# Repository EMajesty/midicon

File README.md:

# MIDI Controller — MCU Pinout and Wiring Reference

MCU: Arduino Mega 2560 Pro  
Logic voltage: 5 V

## 1. MCU Pin Assignments

| Arduino Pin | Net | Function |
|---|---|---|
| D3 | E1_PB | Encoder 1 push button |
| D5 | E1_A | Encoder 1 channel A |
| D7 | E1_B | Encoder 1 channel B |
| D9 | E2_PB | Encoder 2 push button |
| D11 | E2_A | Encoder 2 channel A |
| D14 | E2_B | Encoder 2 channel B |
| D15 | E3_PB | Encoder 3 push button |
| D17 | E3_A | Encoder 3 channel A |
| D18 | MIDI_OUT | MIDI output (TX1) |
| D19 | MIDI_IN | MIDI input (RX1) |
| D21 | E3_B | Encoder 3 channel B |
| D23 | E4_PB | Encoder 4 push button |
| D24 | C1 | Matrix column 1 |
| D25 | E4_A | Encoder 4 channel A |
| D26 | C2 | Matrix column 2 |
| D27 | E4_B | Encoder 4 channel B |
| D28 | C3 | Matrix column 3 |
| D30 | C4 | Matrix column 4 |
| D32 | LEDS | WS2812B data |
| D33 | F1 | Function button 1 |
| D35 | F2 | Function button 2 |
| D36 | LCD_RS | LCD register select |
| D37 | F3 | Function button 3 |
| D38 | LCD_E | LCD enable |
| D39 | F4 | Function button 4 |
| D40 | LCD_DB4 | LCD data bit 4 |
| D41 | R1 | Matrix row 1 |
| D42 | LCD_DB5 | LCD data bit 5 |
| D43 | R2 | Matrix row 2 |
| D44 | LCD_DB6 | LCD data bit 6 |
| D45 | R3 | Matrix row 3 |
| D46 | LCD_DB7 | LCD data bit 7 |
| D47 | R4 | Matrix row 4 |
| A0 | ADC_F1 | Fader 1 |
| A2 | ADC_F2 | Fader 2 |
| A4 | ADC_F3 | Fader 3 |
| A6 | ADC_F4 | Fader 4 |
| A8 | ADC_J1X | Joystick 1 X |
| A10 | ADC_J1Y | Joystick 1 Y |
| A12 | ADC_J2X | Joystick 2 X |
| A14 | ADC_J2Y | Joystick 2 Y |

D0/D1 are reserved for USB serial debugging.

## 2. Rotary Encoders

Four rotary encoders with integrated push buttons.

| Contact | Connection |
|---|---|
| A | E*_A MCU input |
| B | E*_B MCU input |
| Common | GND |
| Push button terminal 1 | E*_PB MCU input |
| Push button terminal 2 | GND |

- All 12 inputs use `INPUT_PULLUP`.
- Rotary contacts pull their respective inputs LOW when closed.
- Push buttons are active LOW.
- Quadrature decoding and debouncing are handled in firmware.

## 3. Function Buttons

Four independent momentary buttons.

| Contact | Connection |
|---|---|
| Terminal 1 | F1–F4 MCU input |
| Terminal 2 | GND |

- Configure as `INPUT_PULLUP`.
- Pressed = LOW.

## 4. Button Matrix

4×4 matrix with one diode per button.

| Row | C1 (D24) | C2 (D26) | C3 (D28) | C4 (D30) |
|---|---|---|---|---|
| R1 (D41) | SW1 | SW2 | SW3 | SW4 |
| R2 (D43) | SW5 | SW6 | SW7 | SW8 |
| R3 (D45) | SW9 | SW10 | SW11 | SW12 |
| R4 (D47) | SW13 | SW14 | SW15 | SW16 |

### Wiring

Each button is wired:

`Column → Switch → Diode anode → Diode cathode → Row`

- Diode cathode (striped end) faces the row.
- One diode per switch prevents ghosting.
- Columns are configured as `INPUT_PULLUP`.
- Scan by driving one row LOW at a time.
- Inactive rows are high-impedance (`INPUT`).
- A pressed button on the active row reads LOW at its column.

## 5. Analog Controls

Four stereo faders (one track used per fader) and two dual-axis joysticks.

| Control | ADC Pin |
|---|---|
| Fader 1 | A0 |
| Fader 2 | A2 |
| Fader 3 | A4 |
| Fader 4 | A6 |
| Joystick 1 X | A8 |
| Joystick 1 Y | A10 |
| Joystick 2 X | A12 |
| Joystick 2 Y | A14 |

### Wiring

Each potentiometer:

| Terminal | Connection |
|---|---|
| End 1 | +5 V |
| Wiper | ADC input |
| End 3 | GND |

- ADC range: 0–1023.
- Reversing the outer terminals reverses the control direction.
- Unused tracks of stereo faders are left unconnected.
- Joystick axes each use one potentiometer.

## 6. WS2812B LEDs

Four addressable RGB LEDs connected in series.

| Signal | Connection |
|---|---|
| First LED DIN | D32 (LEDS) |
| Each LED DOUT | Next LED DIN |
| All VDD | +5 V |
| All VSS | GND |
| Final LED DOUT | Unconnected |

All LEDs are controlled through one MCU pin.

## 7. LCD

20×2 character LCD, 4-bit parallel interface.

Module markings: Winstar WDH0048-TMI-ET#00 / Forewin 2002AE-1.

The following assumes a standard HD44780-compatible 16-pin interface.

| LCD Pin | Signal | Connection |
|---|---|---|
| 1 | VSS | GND |
| 2 | VDD | +5 V |
| 3 | VO | Contrast potentiometer wiper |
| 4 | RS | D36 |
| 5 | R/W | GND |
| 6 | E | D38 |
| 7–10 | DB0–DB3 | Unconnected |
| 11 | DB4 | D40 |
| 12 | DB5 | D42 |
| 13 | DB6 | D44 |
| 14 | DB7 | D46 |
| 15 | LED+ | +5 V (verify current limiting) |
| 16 | LED− | GND |

### Contrast potentiometer (RV9)

| Terminal | Connection |
|---|---|
| End 1 | +5 V |
| Wiper | LCD VO |
| End 3 | GND |

Firmware initialization:

`LiquidCrystal lcd(36, 38, 40, 42, 44, 46);`

## 8. MIDI Input

5-pin DIN MIDI input using a 6N137 optocoupler.

## 9. MIDI Output

5-pin DIN MIDI output driven by hardware UART1.

Firmware:

`Serial1.begin(31250);`

## 10. Power Supply

9 V DC input regulated to 5 V using an L7805.

| Component | Connection |
|---|---|
| Barrel jack positive | +9 V |
| Barrel jack negative | GND |
| L7805 IN | +9 V |
| L7805 GND | GND |
| L7805 OUT | +5 V |
| C2 | Input decoupling |
| C1 | Output decoupling |

The +5 V rail supplies the MCU, controls, LCD, MIDI circuitry and LEDs.

## Firmware and configurator

The v1 firmware is a standalone, four-page configurable MIDI controller. Build it with `pio run -d firmware`; see [firmware/README.md](firmware/README.md) for operation, EEPROM layout, MIDI conventions, and the USB protocol.

The native Python configurator provides JSON validation/import/export, device upload/download, explicit EEPROM save/reload, and a PySide6 GUI:

```sh
python -m pip install -r requirements.txt
python -m configurator validate config/default.json
python -m configurator gui
```

See [configurator/README.md](configurator/README.md) for all commands and [docs/hardware-test-checklist.md](docs/hardware-test-checklist.md) for physical verification.

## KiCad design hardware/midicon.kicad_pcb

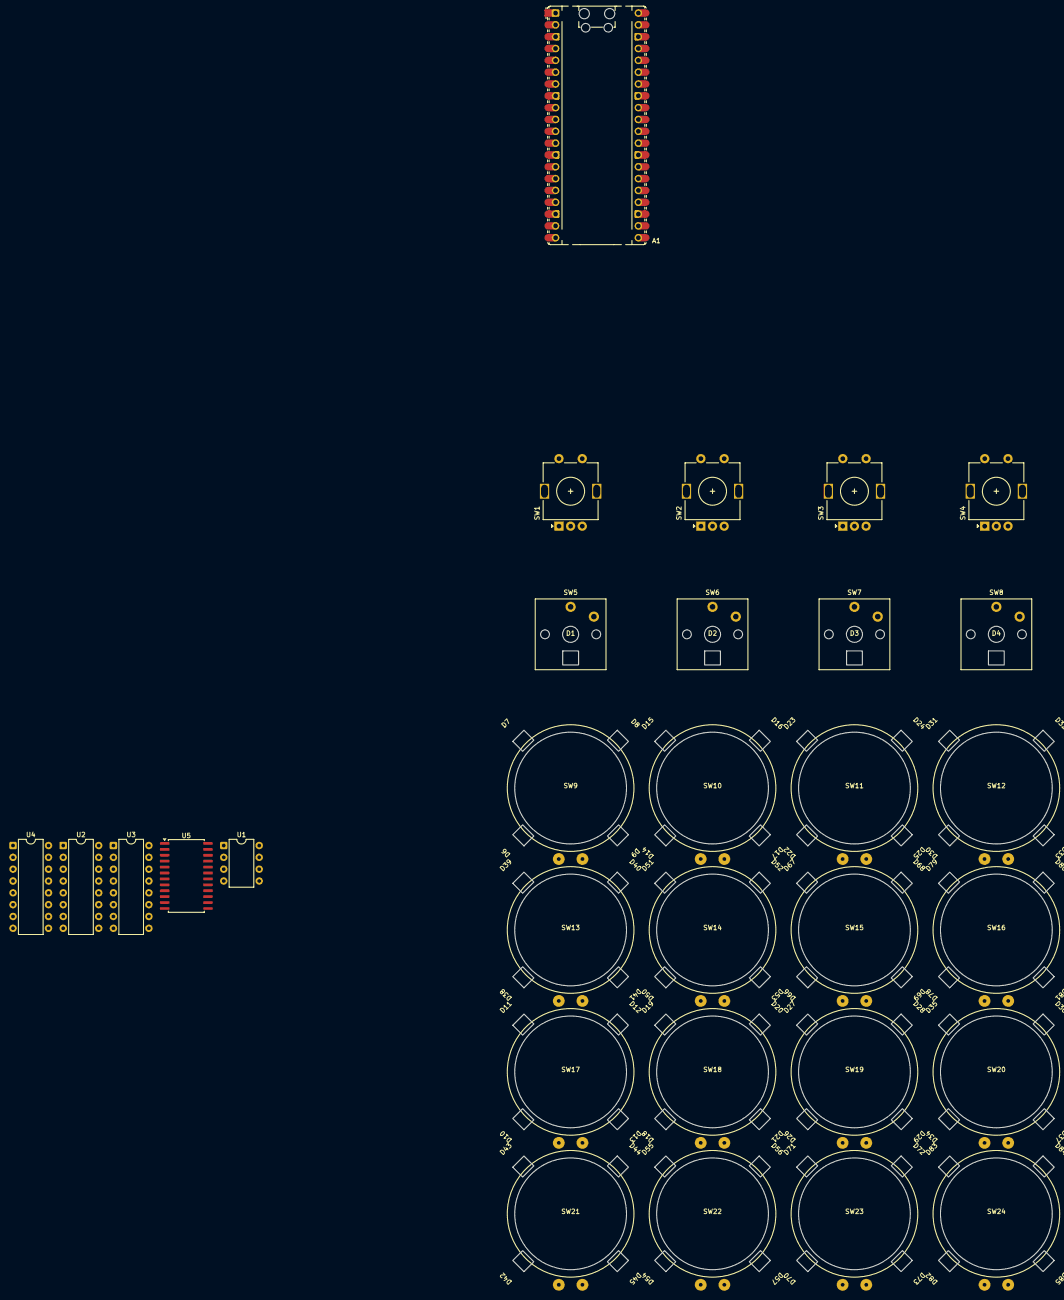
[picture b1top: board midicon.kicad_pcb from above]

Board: 2 copper layers, 98 parts (0 on the bottom side), 103 nets, no tracks yet.

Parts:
A1: RaspberryPi_Pico; RaspberryPi_Pico_Common_Unspecified
D1, D2, D3, D4, D6, D7, D8, D9, D10, D11, D12, D13, D14, D15, D16, D17, D18, D19, D20, D21, D22, D23, D24, D25, D26, D27, D28, D29, D30, D31, D32, D33, D34, D35, D36, D37, D38, D39, D40, D41, D42, D43, D44, D45, D50, D51, D52, D53, D54, D55, D56, D57, D66, D67, D68, D69, D70, D71, D72, D73, D78, D79, D80, D81, D82, D83, D84, D85: WS2812B; SK6812MINIE
SW1, SW2, SW3, SW4: RotaryEncoder_Switch; RotaryEncoder_Alps_EC11E-Switch_Vertical_H20mm
SW5, SW6, SW7, SW8: SW_Push; SW_Kailh_Choc_V1
SW9, SW10, SW11, SW12, SW13, SW14, SW15, SW16, SW17, SW18, SW19, SW20, SW21, SW22, SW23, SW24: SW_Push; Arcade Button
U1: 6N138; DIP-8_W7.62mm
U2, U3: 74HC165; DIP-16_W7.62mm
U4: 74HC595; DIP-16_W7.62mm
U5: HEF4067BT; SOIC-24W_7.5x15.4mm_P1.27mm

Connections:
165_CLK: A1.4 (GPIO2), U2.2 (CP), U3.2 (CP)
165_DATA: A1.6 (GPIO4), U3.9 (Q7)
165_LOAD: A1.5 (GPIO3), U2.1 (~PL), U3.1 (~PL)
595_CLK: A1.9 (GPIO6), U4.11 (SRCLK)
595_DATA: A1.7 (GPIO5), U4.14 (SER)
595_LATCH: A1.10 (GPIO7), U4.12 (RCLK)
4067_S0: A1.11 (GPIO8), U5.10 (A0)
4067_S1: A1.12 (GPIO9), U5.11 (A1)
4067_S2: A1.14 (GPIO10), U5.14 (A2)
4067_S3: A1.15 (GPIO11), U5.13 (A3)
4067_SIG: A1.31 (GPIO26_ADC0), U5.1 (Z)
+3.3V: A1.36 (3V3), U2.16 (VCC), U3.16 (VCC), U4.10 (~SRCLR), U4.16 (VCC), U5.24 (VDD)
+5V: A1.40 (VBUS), D1.1 (VDD), D2.1 (VDD), D3.1 (VDD), D4.1 (VDD), D6.1 (VDD), D7.1 (VDD), D8.1 (VDD), D9.1 (VDD), D10.1 (VDD), D11.1 (VDD), D12.1 (VDD), D13.1 (VDD), D14.1 (VDD), D15.1 (VDD), D16.1 (VDD), D17.1 (VDD), D18.1 (VDD), D19.1 (VDD), D20.1 (VDD), D21.1 (VDD), D22.1 (VDD), D23.1 (VDD), D24.1 (VDD), D25.1 (VDD), D26.1 (VDD), D27.1 (VDD), D28.1 (VDD), D29.1 (VDD), D30.1 (VDD), D31.1 (VDD), D32.1 (VDD), D33.1 (VDD), D34.1 (VDD), D35.1 (VDD), D36.1 (VDD), D37.1 (VDD), D38.1 (VDD), D39.1 (VDD), D40.1 (VDD), D41.1 (VDD), D42.1 (VDD), D43.1 (VDD), D44.1 (VDD), D45.1 (VDD), D50.1 (VDD), D51.1 (VDD), D52.1 (VDD), D53.1 (VDD), D54.1 (VDD), D55.1 (VDD), D56.1 (VDD), D57.1 (VDD), D66.1 (VDD), D67.1 (VDD), D68.1 (VDD), D69.1 (VDD), D70.1 (VDD), D71.1 (VDD), D72.1 (VDD), D73.1 (VDD), D78.1 (VDD), D79.1 (VDD), D80.1 (VDD), D81.1 (VDD), D82.1 (VDD), D83.1 (VDD), D84.1 (VDD), D85.1 (VDD), U1.8 (VCC)
C1: A1.21 (GPIO16), SW9.1, SW13.1, SW17.1, SW21.1
C2: A1.22 (GPIO17), SW10.1, SW14.1, SW18.1, SW22.1
C3: A1.24 (GPIO18), SW11.1, SW15.1, SW19.1, SW23.1
C4: A1.25 (GPIO19), SW12.1, SW16.1, SW20.1, SW24.1
E1_A: SW1.A, U2.12 (D1)
E1_B: SW1.B, U2.13 (D2)
E1_PB: SW1.S1, U2.11 (D0)
E2_A: SW2.A, U2.3 (D4)
E2_B: SW2.B, U2.4 (D5)
E2_PB: SW2.S1, U2.14 (D3)
E3_A: SW3.A, U2.6 (D7)
E3_B: SW3.B, U3.11 (D0)
E3_PB: SW3.S1, U2.5 (D6)
E4_A: SW4.A, U3.13 (D2)
E4_B: SW4.B, U3.14 (D3)
E4_PB: SW4.S1, U3.12 (D1)
F1: SW5.1, U3.3 (D4)
F2: SW6.1, U3.4 (D5)
F3: SW7.1, U3.5 (D6)
F4: SW8.1, U3.6 (D7)
GND: A1.3 (GND), A1.8 (GND), A1.13 (GND), A1.18 (GND), A1.23 (GND), A1.28 (GND), A1.38 (GND), D1.3 (VSS), D2.3 (VSS), D3.3 (VSS), D4.3 (VSS), D6.3 (VSS), D7.3 (VSS), D8.3 (VSS), D9.3 (VSS), D10.3 (VSS), D11.3 (VSS), D12.3 (VSS), D13.3 (VSS), D14.3 (VSS), D15.3 (VSS), D16.3 (VSS), D17.3 (VSS), D18.3 (VSS), D19.3 (VSS), D20.3 (VSS), D21.3 (VSS), D22.3 (VSS), D23.3 (VSS), D24.3 (VSS), D25.3 (VSS), D26.3 (VSS), D27.3 (VSS), D28.3 (VSS), D29.3 (VSS), D30.3 (VSS), D31.3 (VSS), D32.3 (VSS), D33.3 (VSS), D34.3 (VSS), D35.3 (VSS), D36.3 (VSS), D37.3 (VSS), D38.3 (VSS), D39.3 (VSS), D40.3 (VSS), D41.3 (VSS), D42.3 (VSS), D43.3 (VSS), D44.3 (VSS), D45.3 (VSS), D50.3 (VSS), D51.3 (VSS), D52.3 (VSS), D53.3 (VSS), D54.3 (VSS), D55.3 (VSS), D56.3 (VSS), D57.3 (VSS), D66.3 (VSS), D67.3 (VSS), D68.3 (VSS), D69.3 (VSS), D70.3 (VSS), D71.3 (VSS), D72.3 (VSS), D73.3 (VSS), D78.3 (VSS), D79.3 (VSS), D80.3 (VSS), D81.3 (VSS), D82.3 (VSS), D83.3 (VSS), D84.3 (VSS), D85.3 (VSS), SW1.C, SW1.S2, SW2.C, SW2.S2, SW3.C, SW3.S2, SW4.C, SW4.S2, SW5.2, SW6.2, SW7.2, SW8.2, U1.5 (GND), U2.8 (GND), U2.10 (DS), U2.15 (~CE), U3.8 (GND), U3.15 (~CE), U4.8 (GND), U4.13 (~OE), U5.12 (VSS), U5.15 (~E)
MCU_LEDS: A1.26 (GPIO20), D1.4 (DIN)
MIDI_IN: A1.2 (GPIO1), U1.6 (VO2)
unnamed: D1.2 (DOUT), D2.4 (DIN)
unnamed: D2.2 (DOUT), D3.4 (DIN)
unnamed: D3.2 (DOUT), D4.4 (DIN)
unnamed: D6.2 (DOUT), D7.4 (DIN)
unnamed: D7.2 (DOUT), D8.4 (DIN)
unnamed: D8.2 (DOUT), D9.4 (DIN)
unnamed: D10.4 (DIN), D81.2 (DOUT)
unnamed: D10.2 (DOUT), D11.4 (DIN)
unnamed: D11.2 (DOUT), D12.4 (DIN)
unnamed: D12.2 (DOUT), D13.4 (DIN)
unnamed: D13.2 (DOUT), D18.4 (DIN)
unnamed: D9.2 (DOUT), D14.4 (DIN)
unnamed: D14.2 (DOUT), D15.4 (DIN)
unnamed: D15.2 (DOUT), D16.4 (DIN)
unnamed: D16.2 (DOUT), D17.4 (DIN)
unnamed: D17.2 (DOUT), D22.4 (DIN)
unnamed: D18.2 (DOUT), D19.4 (DIN)
unnamed: D19.2 (DOUT), D20.4 (DIN)
unnamed: D20.2 (DOUT), D21.4 (DIN)
unnamed: D21.2 (DOUT), D26.4 (DIN)
unnamed: D22.2 (DOUT), D23.4 (DIN)
unnamed: D23.2 (DOUT), D24.4 (DIN)
unnamed: D24.2 (DOUT), D25.4 (DIN)
unnamed: D25.2 (DOUT), D30.4 (DIN)
unnamed: D26.2 (DOUT), D27.4 (DIN)
unnamed: D27.2 (DOUT), D28.4 (DIN)
unnamed: D28.2 (DOUT), D29.4 (DIN)
unnamed: D29.2 (DOUT), D34.4 (DIN)
unnamed: D30.2 (DOUT), D31.4 (DIN)
unnamed: D31.2 (DOUT), D32.4 (DIN)
unnamed: D32.2 (DOUT), D33.4 (DIN)
unnamed: D33.2 (DOUT), D38.4 (DIN)
unnamed: D34.2 (DOUT), D35.4 (DIN)
unnamed: D35.2 (DOUT), D36.4 (DIN)
unnamed: D36.2 (DOUT), D37.4 (DIN)
unnamed: D37.2 (DOUT), D42.4 (DIN)
unnamed: D38.2 (DOUT), D39.4 (DIN)
unnamed: D39.2 (DOUT), D40.4 (DIN)
unnamed: D40.2 (DOUT), D41.4 (DIN)
unnamed: D41.2 (DOUT), D50.4 (DIN)
unnamed: D42.2 (DOUT), D43.4 (DIN)
unnamed: D43.2 (DOUT), D44.4 (DIN)
unnamed: D44.2 (DOUT), D45.4 (DIN)
unnamed: D45.2 (DOUT), D54.4 (DIN)
unnamed: D50.2 (DOUT), D51.4 (DIN)
unnamed: D51.2 (DOUT), D52.4 (DIN)
unnamed: D52.2 (DOUT), D53.4 (DIN)
unnamed: D53.2 (DOUT), D66.4 (DIN)
unnamed: D54.2 (DOUT), D55.4 (DIN)
unnamed: D55.2 (DOUT), D56.4 (DIN)
unnamed: D56.2 (DOUT), D57.4 (DIN)
unnamed: D57.2 (DOUT), D70.4 (DIN)
unnamed: D66.2 (DOUT), D67.4 (DIN)
unnamed: D67.2 (DOUT), D68.4 (DIN)
unnamed: D68.2 (DOUT), D69.4 (DIN)
unnamed: D69.2 (DOUT), D78.4 (DIN)
unnamed: D70.2 (DOUT), D71.4 (DIN)
unnamed: D71.2 (DOUT), D72.4 (DIN)
unnamed: D72.2 (DOUT), D73.4 (DIN)
unnamed: D73.2 (DOUT), D82.4 (DIN)
unnamed: D78.2 (DOUT), D79.4 (DIN)
unnamed: D79.2 (DOUT), D80.4 (DIN)
unnamed: D80.2 (DOUT), D81.4 (DIN)
unnamed: D82.2 (DOUT), D83.4 (DIN)
unnamed: D83.2 (DOUT), D84.4 (DIN)
unnamed: D84.2 (DOUT), D85.4 (DIN)
unnamed: U2.9 (Q7), U3.10 (DS)
